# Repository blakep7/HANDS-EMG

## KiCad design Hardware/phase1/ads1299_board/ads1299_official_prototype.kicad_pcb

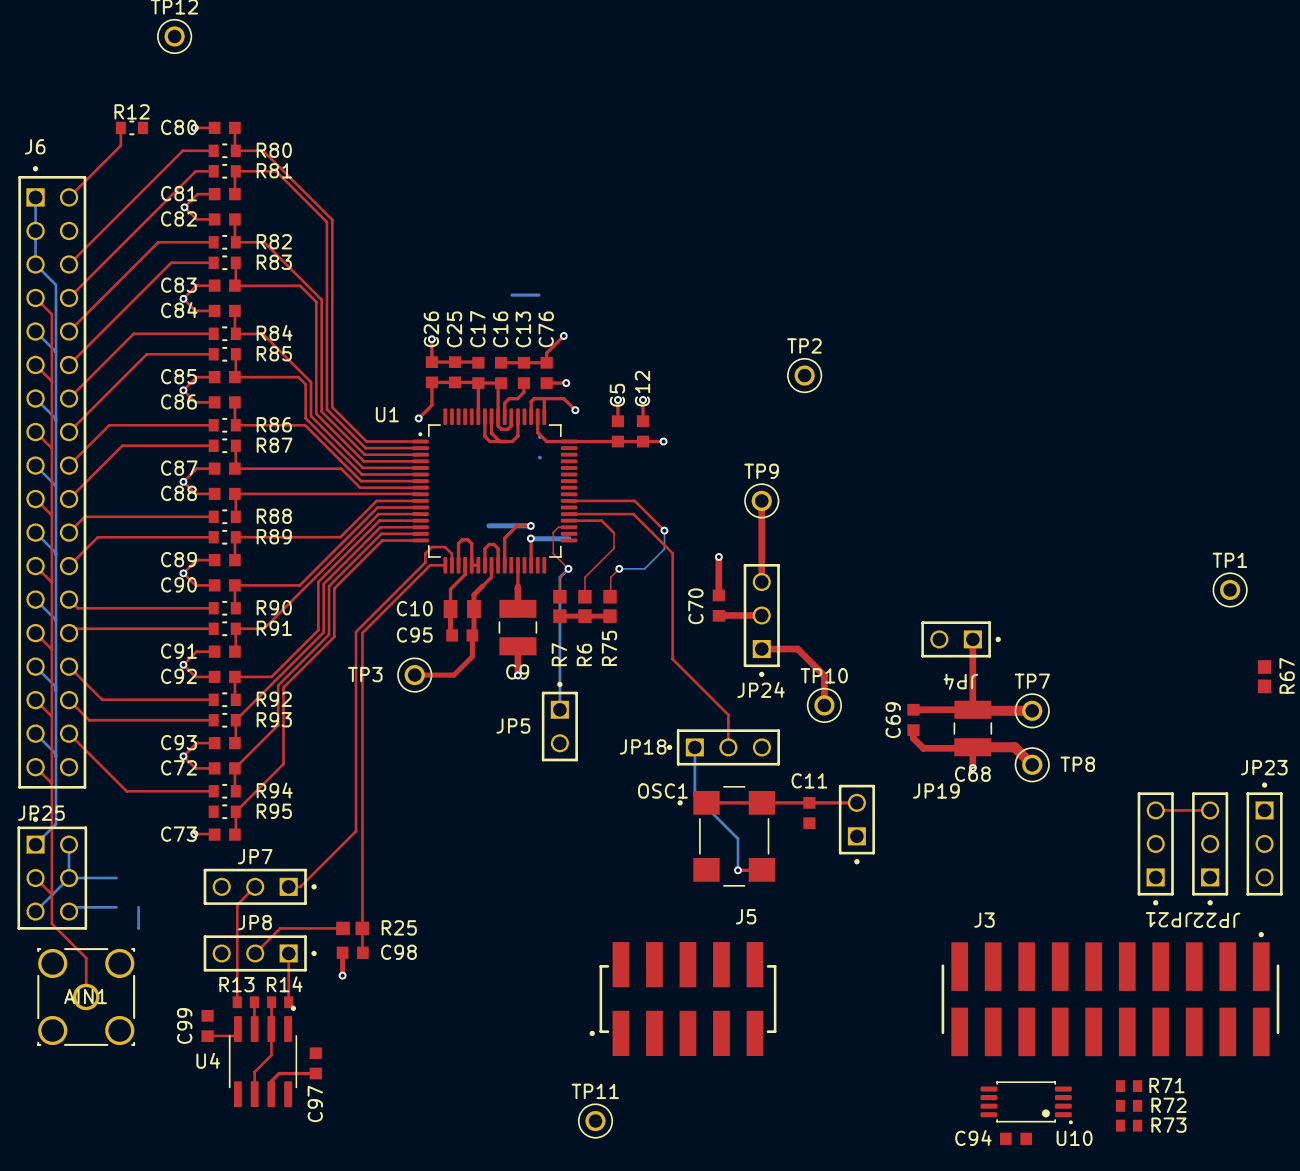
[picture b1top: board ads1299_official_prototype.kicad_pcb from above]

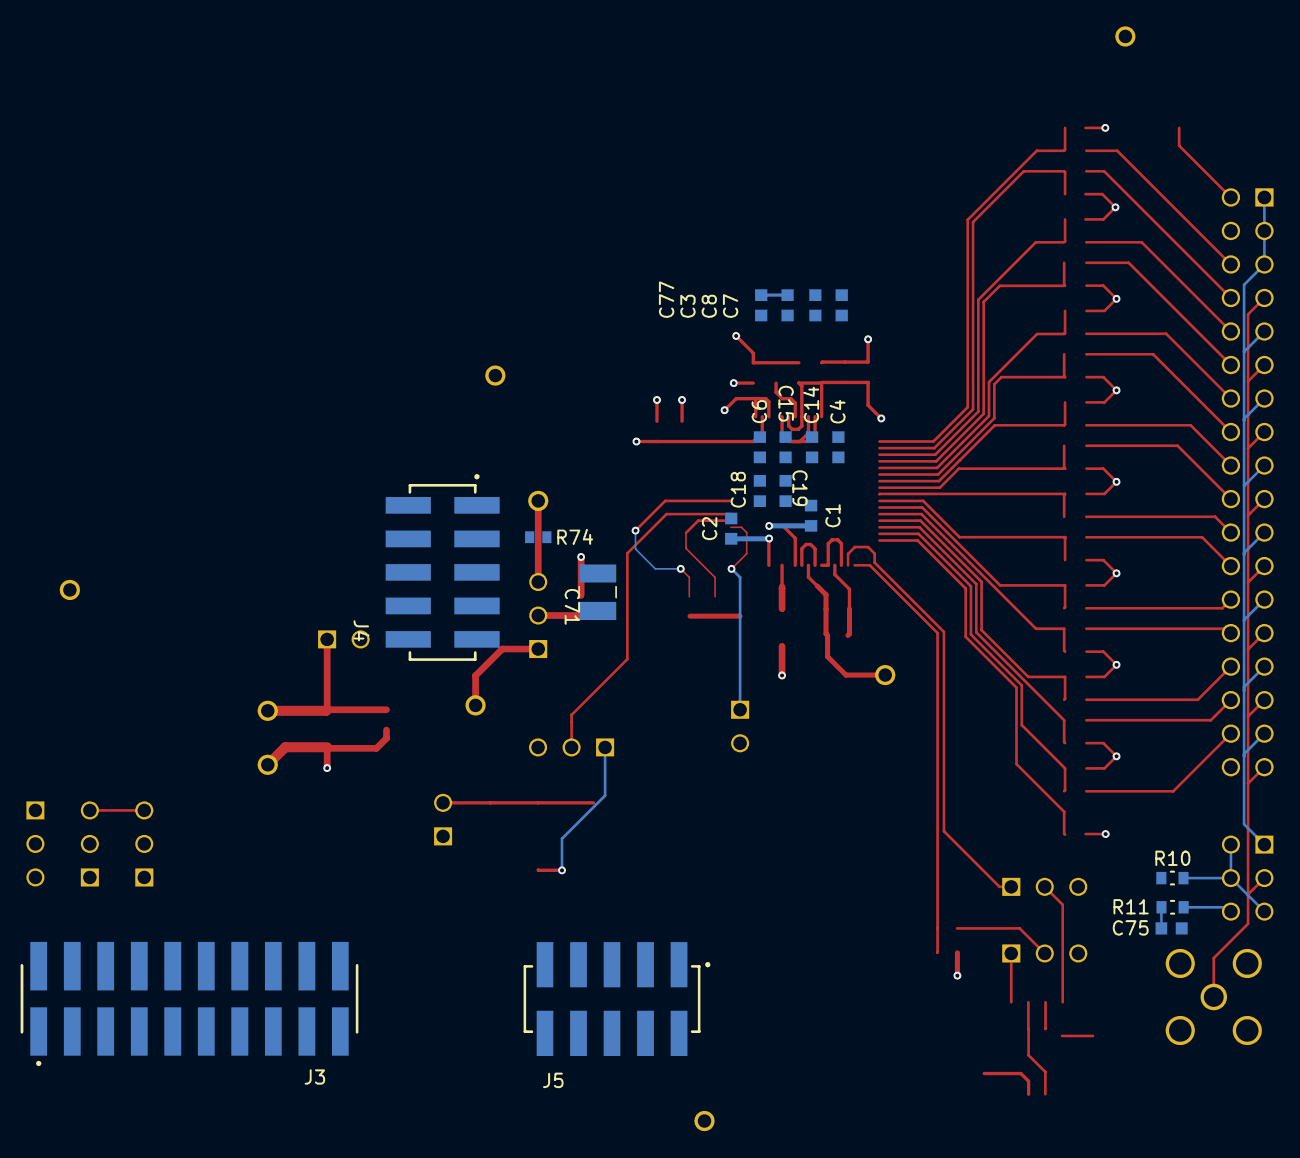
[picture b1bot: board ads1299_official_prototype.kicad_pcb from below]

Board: 4 copper layers, 110 parts (20 on the bottom side), 78 nets.

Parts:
AIN1: AIN1; 132134_AMP
C1, C2, C3, C4, C5, C6, C7, C8, C11, C17, C25, C76, C77, C97, C99: 1uF; CAPC1608X90N
C9, C68, C71: 100uF; CAPC3225X280N
C10: 10uF; CAPC2012X95N
C12, C13, C14, C15, C16, C18, C19, C26, C69, C70, C94, C95: 0.1uF; CAPC1608X90N
C72, C73, C75, C80, C81, C82, C83, C84, C85, C86, C87, C88, C89, C90, C91, C92, C93: 4.7nF; CAPC1608X90N
C98: 0.01uF; CAPC1608X90N
J3, J3#2: Conn_02x10_Odd_Even; SAMTEC_TSM-110-01-T-DV-P-TR
J4, J5, J5#2: SAMTEC_SSW-105-22-F-D-VS-K
J6: 36PIN_IDC; SAMTEC_SSW-118-21-F-D
JP4, JP5, JP19: TSW-102-07-T-S; SAMTEC_TSW-102-07-T-S
JP7, JP8, JP18, JP21, JP22, JP23, JP24: TSW-103-07-T-S; SAMTEC_TSW-103-07-T-S
JP25: TSW-103-07-T-D; SAMTEC_TSW-103-07-T-D
OSC1: HC735-2.048MHZ; XTAL_FXO-HC735-8
R6, R7, R67, R75: 10K; RESC1607X60N
R10, R11, R12, R80, R81, R82, R83, R84, R85, R86, R87, R88, R89, R90, R91, R92, R93, R94, R95: 4.99K; RESC1608X60N
R13, R14, R71, R72, R73, R74: 0; RESC1005X40
R25: 0; RESC1607X60N
TP1, TP2, TP8, TP11, TP12: 5001; KEYSTONE_5001
TP3: 5000; KEYSTONE_5000
TP7, TP9, TP10: 5001; KEYSTONE_5000
U1: ADS1299IPAG; QFP64P50_1200X1200X120L60X22N
U4: OPA376; SOIC127P599X175-8N
U10: 24AA256-I/ST; SOP8P65_300X640X120L60X24N

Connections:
1: J6.01, J6.03, J6.05, J6.09, J6.13, J6.17, J6.21, J6.25, J6.29, J6.33, JP25.01
6: J6.06, R80.2
8: J6.08, R81.2
10: J6.10, R82.2
11: AIN1.1, J6.07, J6.11, J6.15, J6.19, J6.23, J6.27, J6.31, J6.35, JP25.03
12: J6.12, R83.2
14: J6.14, R84.2
16: J6.16, R85.2
18: J6.18, R86.2
20: J6.20, R87.2
22: J6.22, R88.2
24: J6.24, R89.2
26: J6.26, R90.2
28: J6.28, R91.2
30: J6.30, R92.2
32: J6.32, R93.2
34: J6.34, R94.2
36: J6.36, R95.2
+3V3: C94.1, R71.2, R72.2, R73.2, U10.1, U10.2, U10.3, U10.8
+5V: C68.1, C69.1, JP4.01, TP7.TP
/SCL: J3.16, J3#2.16, U10.6
/SDA: J3.20, J3#2.20, U10.5
AIN1N: C72.1, R94.1, U1.15 (IN1N)
AIN1P: C73.2, R95.1, U1.16 (IN1P)
AIN2N: C92.1, R92.1, U1.13 (IN2N)
AIN2P: C93.2, R93.1, U1.14 (IN2P)
AIN3N: C90.1, R90.1, U1.11 (IN3N)
AIN3P: C91.2, R91.1, U1.12 (IN3P)
AIN4N: C88.1, R88.1, U1.9 (IN4N)
AIN4P: C89.2, R89.1, U1.10 (IN4P)
AIN5N: C86.1, R86.1, U1.7 (IN5N)
AIN5P: C87.2, R87.1, U1.8 (IN5P)
AIN6N: C84.1, R84.1, U1.5 (IN6N)
AIN6P: C85.2, R85.1, U1.6 (IN6P)
AIN7N: C82.1, R82.1, U1.3 (IN7N)
AIN7P: C83.2, R83.1, U1.4 (IN7P)
AIN8N: C80.1, R80.1, U1.1 (IN8N)
AIN8P: C81.2, R81.1, U1.2 (IN8P)
AVDD: C4.1, C6.1, C7.1, C8.1, C14.1, C15.1, C16.1, C17.1, C18.1, C19.1, C25.1, C26.1, C97.1, U1.19 (AVDD), U1.21 (AVDD), U1.22 (AVDD), U1.54 (AVDD1), U1.56 (AVDD), U1.59 (AVDD), U4.7 (V+)
AVSS: C1.2, C2.2, C3.2, C4.2, C6.2, C8.2, C9.2, C10.2, C13.2, C14.2, C15.2, C16.2, C76.1, C77.1, C95.2, U1.20 (AVSS), U1.23 (AVSS), U1.25 (VREFN), U1.32 (AVSS), U1.53 (AVSS1), U1.57 (AVSS), U1.58 (AVSS)
CLK: JP18.02, U1.37 (CLK)
CLKSEL: JP23.02, R67.2, U1.52 (CLKSEL)
DVDD: C5.1, C12.1, C70.1, C71.1, JP19.01, JP24.02, R6.1, R7.1, R67.1, R75.1, U1.48 (DVDD), U1.50 (DVDD)
EXT_CLK: J3.17, J3#2.17, JP18.03
GND: C68.2, C69.2, C94.2, JP23.01, R71.1, R72.1, R73.1, R74.1, TP8.TP, U10.4, U10.7
GNDA: C5.2, C7.2, C11.2, C12.2, C17.2, C18.2, C19.2, C25.2, C26.2, C70.2, C71.2, C72.2, C73.1, C75.2, C76.2, C77.2, C80.2, C81.1, C82.2, C83.1, C84.2, C85.1, C86.2, C87.1, C88.2, C89.1, C90.2, C91.1, C92.2, C93.1, C97.2, C98.2, C99.2, J3.10, J3.18, J3#2.10, J3#2.18, JP5.02, OSC1.2 (GND), R74.2, TP1.TP, TP2.TP, TP11.TP, TP12.TP, U1.31 (RESV1), U1.33 (DGND), U1.49 (DGND), U1.51 (DGND), U1.64 (RESERVED)
GPIO2: J3.12, J3#2.12, U1.44 (GPIO2)
unnamed: JP21.03, JP22.03
unnamed: J3.14, J3#2.14, JP22.01
unnamed: JP24.03, TP9.TP
unnamed: JP24.01, TP10.TP
unnamed: J4.10, JP4.02
unnamed: J6.02, R12.1
unnamed: JP7.02, R13.2
unnamed: JP8.01, R14.1
unnamed: JP8.02, R25.2
unnamed: JP25.02, JP25.04, JP25.05, R10.1
unnamed: JP25.06, R11.1
unnamed: C11.1, JP19.02, OSC1.1 (E/D), OSC1.4 (VDD)
unnamed: JP18.01, OSC1.3 (OUTPUT)
unnamed: R13.1, U4.3 (+IN)
unnamed: R14.2, U4.2 (-IN), U4.6 (OUT)
unnamed: C99.1, U4.4 (V-)
REF_ELEC: C75.1, JP7.03, JP8.03, R11.2
SPI_CS: JP21.02, R75.2, U1.39 (*CS)
SPI_DRDY: J3.15, J3#2.15, U1.47 (*DRDY)
SPI_IN: J3.11, J3#2.11, U1.34 (DIN)
SPI_OUT: J3.13, J3#2.13, U1.43 (DOUT)
SPI_START: JP22.02, U1.38 (START)
SRB1: C98.1, R25.1, U1.17 (SRB1)
SRB2: JP7.01, U1.18 (SRB2)
VCAP1: C9.1, U1.28 (VCAP1)
VCAP2: C2.1, U1.30 (VCAP2)
VCAP3: C3.1, C13.1, U1.55 (VCAP3)
VCAP4: C1.1, U1.26 (VCAP4)
VREFP: C10.1, C95.1, TP3.TP, U1.24 (VREFP)
/PWDN: JP5.01, R7.2, U1.35 (*PWDN)
/RESET: R6.2, U1.36 (*RESET)

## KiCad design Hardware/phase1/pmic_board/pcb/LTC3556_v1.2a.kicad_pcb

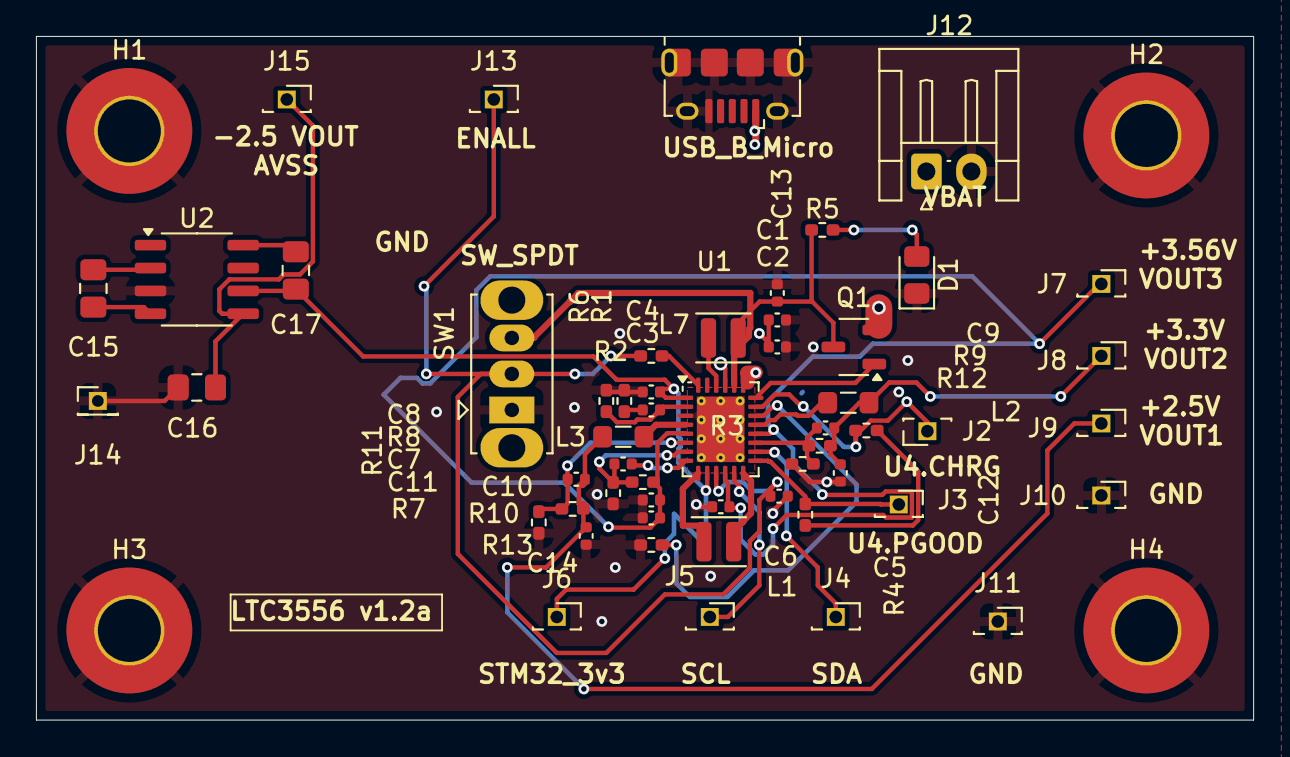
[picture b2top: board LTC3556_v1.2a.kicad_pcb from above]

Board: 4 copper layers, 67.6 x 38.0 mm, 58 parts (0 on the bottom side), 33 nets.

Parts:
C1, C11, C12, C13, C14: 10uF; C_0402_1005Metric
C2, C3, C4: 100nF; C_0402_1005Metric
C5, C6, C7: 1uF; C_0402_1005Metric
C8: 130pF; C_0402_1005Metric
C9, C10: 10pF; C_0402_1005Metric
C15, C16, C17: 10uF; C_0805_2012Metric_Pad1.18x1.45mm_HandSolder
D1: LED; LED_0805_2012Metric_Pad1.15x1.40mm_HandSolder
H1, H2, H3, H4: MountingHole_Pad; MountingHole_3.5mm_Pad_TopBottom
J1: USB_B_Micro; USB_Micro-B_Amphenol_10118194-0001LF_Horizontal
J2, J3, J4, J5, J6, J7, J8, J9, J10, J11, J13, J15: Conn_01x01_Pin; PinSocket_1x01_P1.27mm_Vertical
J12: Conn_01x02_Pin; JST_EH_S2B-EH_1x02_P2.50mm_Horizontal
J14: Conn_01x01_Pin; PinHeader_1x01_P1.27mm_Vertical
L1: 2.2uH/1.6A; L_APV_ANR252010
L2, L3: 4.7uH/500mA; L_0805_2012Metric_Pad1.05x1.20mm_HandSolder
L7: 3.3uH/1.7A; L_APV_ANR252010
Q1: SI2333DS-T1-E3; SOT-23-3
R1: 8.25 Ohm; R_0402_1005Metric_Pad0.72x0.64mm_HandSolder
R2: ZERO Ohm; R_0402_1005Metric_Pad0.72x0.64mm_HandSolder
R3, R4: 10K; R_0402_1005Metric_Pad0.72x0.64mm_HandSolder
R5: 510; R_0402_1005Metric_Pad0.72x0.64mm_HandSolder
R6: 3.01K; R_0402_1005Metric_Pad0.72x0.64mm_HandSolder
R7: 2K; R_0402_1005Metric_Pad0.72x0.64mm_HandSolder
R8: 383K; R_0402_1005Metric_Pad0.72x0.64mm_HandSolder
R9: 347K; R_0402_1005Metric_Pad0.72x0.64mm_HandSolder
R10: 235K; R_0402_1005Metric_Pad0.72x0.64mm_HandSolder
R11, R12, R13: 111K; R_0402_1005Metric_Pad0.72x0.64mm_HandSolder
SW1: SW_SPDT; SW_Slide_SPDT_Straight_CK_OS102011MS2Q
U1: LTC3556EUFD_PBF; QFN-28-1EP_4x5mm_P0.5mm_EP2.65x3.65mm_ThermalVias
U2: SO-8_3.9x4.9mm_P1.27mm

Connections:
GND: C1.2, C2.2, C4.1, C5.1, C6.1, C7.1, C11.2, C12.2, C13.2, C14.2, C16.1, D1.1 (K), H1.1, H2.1, H3.1, H4.1, J1.5 (GND), J1.6 (Shield), J10.1, J11.1, J12.2, J14.1, R1.2, R6.2, R7.2, R11.2, R12.2, R13.2, SW1.1 (A), U1.3 (NTC), U1.29 (EPAD), U2.3 (GND)
unnamed: C3.1, R1.1
unnamed: D1.2 (A), R5.2
unnamed: C1.1, C2.1, J1.1 (VBUS), U1.25 (VBUS)
unnamed: J2.1, R3.2, U1.21 (*CHRG)
unnamed: J3.1, R4.2, U1.15 (PGOODALL)
unnamed: J4.1, U1.16 (SDA)
unnamed: J5.1, U1.13 (SCL)
unnamed: C4.2, C17.1, J6.1, U1.1 (LDO3V3), U1.10 (DVCC), U2.6 (LV)
unnamed: C16.2, J15.1, U2.5 (V_OUT2.5V)
unnamed: Q1.1 (G), U1.22 (GATE)
unnamed: C13.1, L7.1, Q1.2 (S), R5.1, SW1.3 (C), U1.24 (VOUT)
unnamed: C3.2, R6.1, U1.2 (CLPROG)
unnamed: R2.2, U1.28 (ENALL)
unnamed: C10.2, R10.2, R13.1, U1.6 (FB1)
unnamed: C9.2, R9.2, R12.1, U1.17 (FB2)
unnamed: C8.1, R8.2, R11.1, U1.7 (FB3)
unnamed: R7.1, U1.20 (PROG)
unnamed: L3.2, U1.4 (SW1)
unnamed: L2.2, U1.19 (SW2)
unnamed: L7.2, U1.26 (SW)
unnamed: L1.2, U1.9 (SWAB3)
unnamed: L1.1, U1.14 (SWCD3)
unnamed: C8.2, U1.8 (VC3)
unnamed: C15.1, U2.2 (CAP+)
unnamed: C15.2, U2.4 (CAP-)
unnamed: C17.2, U2.8 (V+)
VBAT: J12.1, Q1.3 (D), U1.23 (BAT)
VCC: R3.1, R4.1
VOUT0: C5.2, J13.1, R2.1, SW1.2 (B), U1.11 (VIN3)
VOUT1: C10.1, C14.1, J9.1, L3.1, R10.1
VOUT2: C9.1, C12.1, J8.1, L2.1, R9.1
VOUT3: C6.2, C7.2, C11.1, J7.1, R8.1, U1.5 (VIN1), U1.12 (VOUT3), U1.18 (VIN2)
